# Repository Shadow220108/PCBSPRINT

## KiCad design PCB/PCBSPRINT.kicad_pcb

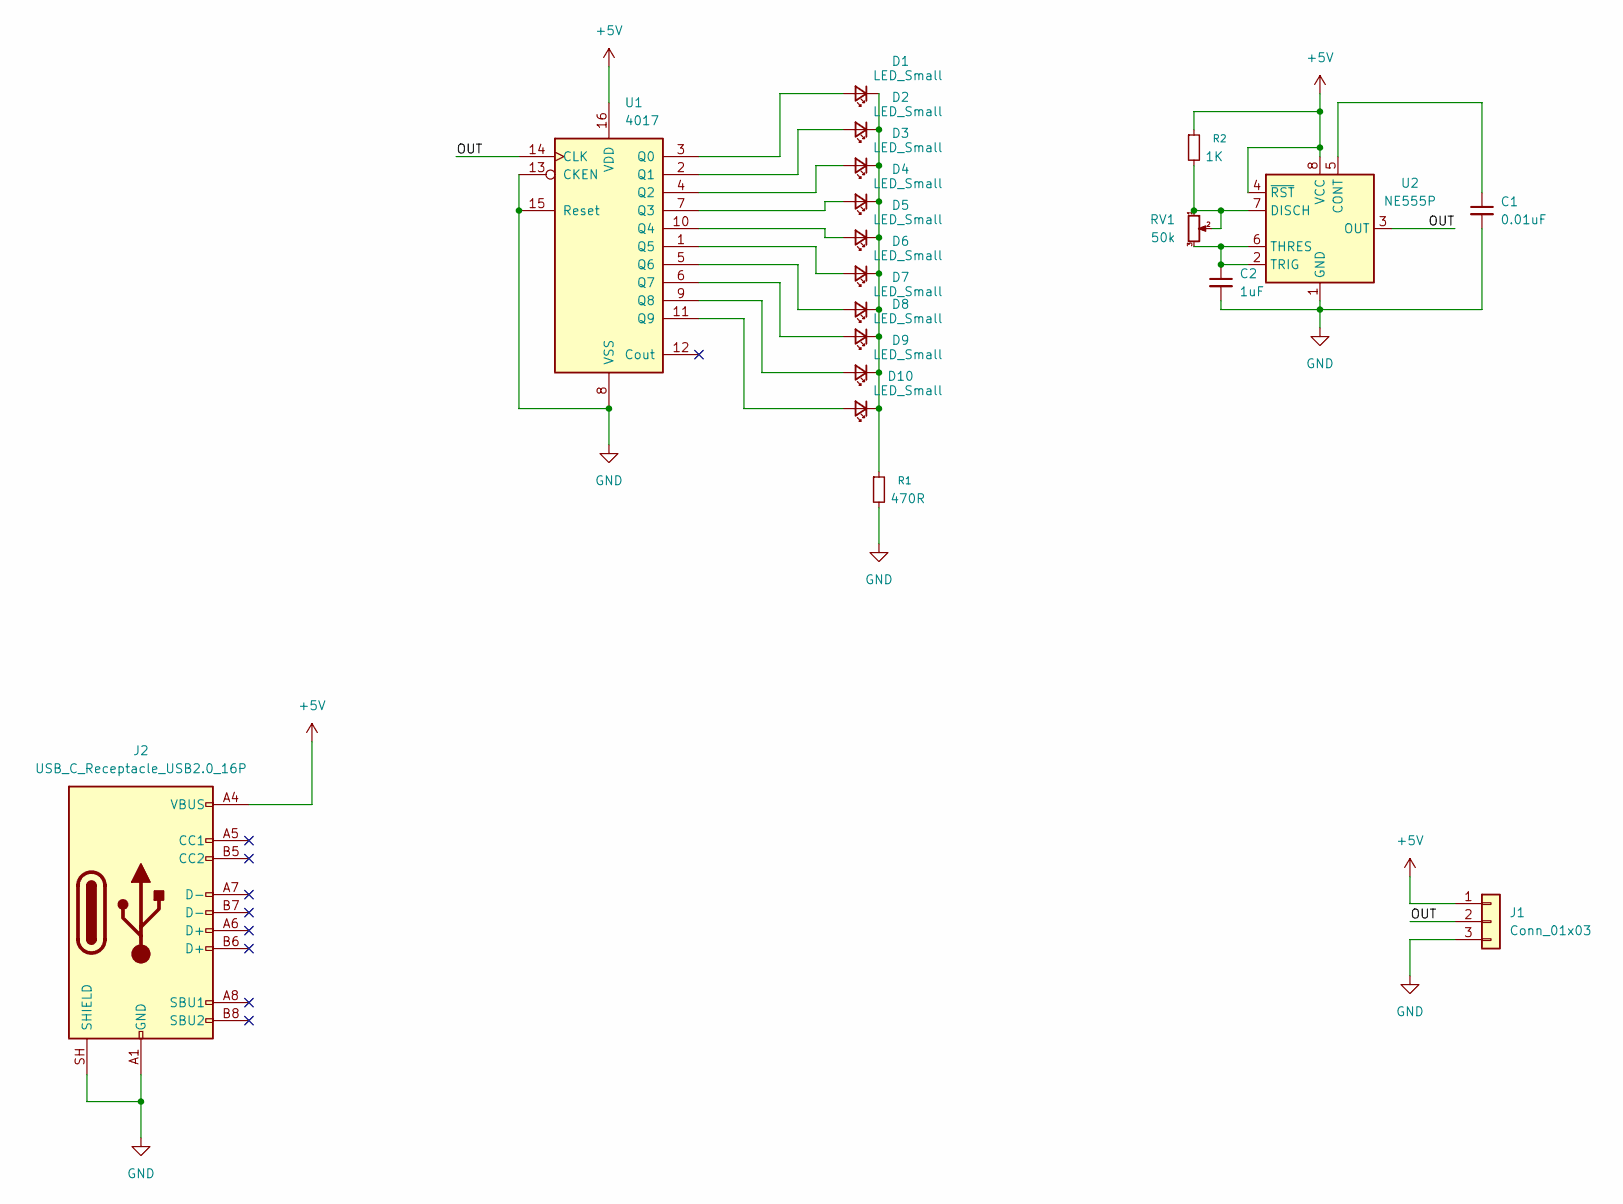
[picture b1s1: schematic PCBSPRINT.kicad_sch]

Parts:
C1: 0.01uF; C_0805_2012Metric_Pad1.18x1.45mm_HandSolder
C2: 1uF; C_0805_2012Metric_Pad1.18x1.45mm_HandSolder
D1, D2, D3, D4, D5, D6, D7, D8, D9, D10: LED_Small; LED_2512_6332Metric_Pad1.52x3.35mm_HandSolder
J1: Conn_01x03; PinHeader_1x03_P2.54mm_Vertical
J2: USB_C_Receptacle_USB2.0_16P; USB_C_Receptacle_HRO_TYPE-C-31-M-12
R1: 470R; R_0805_2012Metric_Pad1.20x1.40mm_HandSolder
R2: 1K; R_0805_2012Metric_Pad1.20x1.40mm_HandSolder
RV1: 50k; Potentiometer_Vishay_T93YA_Vertical
U1: 4017; DIP-16_16P-L20.2-W6.6-P2.54-LS7.6-BL
U2: NE555P; DIP-8_W7.62mm

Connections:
+5V: J1.1, J2.A4 (VBUS), J2.A9 (VBUS), J2.B4 (VBUS), J2.B9 (VBUS), R2.1, U1.16 (VDD), U2.4 (~RST), U2.8 (VCC)
/OUT: J1.2, U1.14 (CLK), U2.3 (OUT)
GND: C1.2, C2.2, J1.3, J2.A1 (GND), J2.A12 (GND), J2.B1 (GND), J2.B12 (GND), J2.SH (SHIELD), R1.2, U1.8 (VSS), U1.13 (CKEN), U1.15 (Reset), U2.1 (GND)
unnamed: D1.2 (A), U1.3 (Q0)
unnamed: D1.1 (K), D2.1 (K), D3.1 (K), D4.1 (K), D5.1 (K), D6.1 (K), D7.1 (K), D8.1 (K), D9.1 (K), D10.1 (K), R1.1
unnamed: D2.2 (A), U1.2 (Q1)
unnamed: D3.2 (A), U1.4 (Q2)
unnamed: D4.2 (A), U1.7 (Q3)
unnamed: D5.2 (A), U1.10 (Q4)
unnamed: D6.2 (A), U1.1 (Q5)
unnamed: D7.2 (A), U1.5 (Q6)
unnamed: D8.2 (A), U1.6 (Q7)
unnamed: D9.2 (A), U1.9 (Q8)
unnamed: D10.2 (A), U1.11 (Q9)
unnamed: C1.1, U2.5 (CONT)
unnamed: R2.2, RV1.1, RV1.2, U2.7 (DISCH)
unnamed: C2.1, RV1.3, U2.2 (TRIG), U2.6 (THRES)

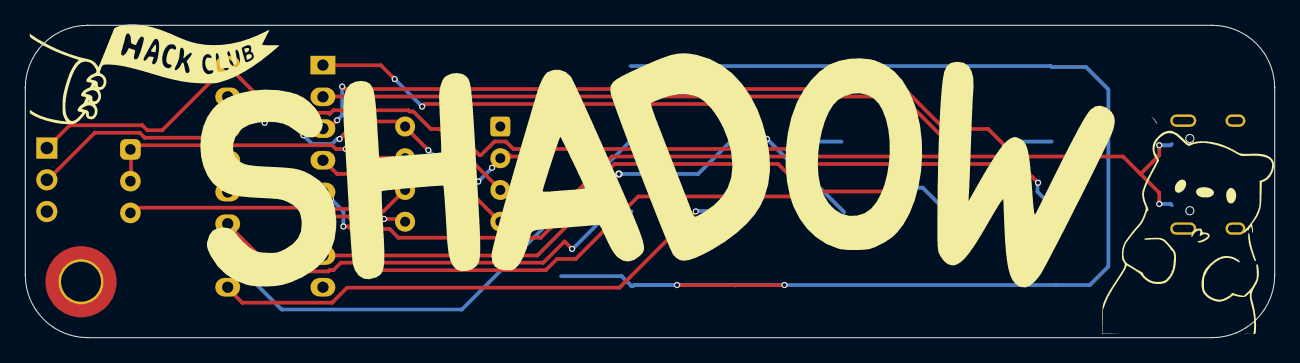
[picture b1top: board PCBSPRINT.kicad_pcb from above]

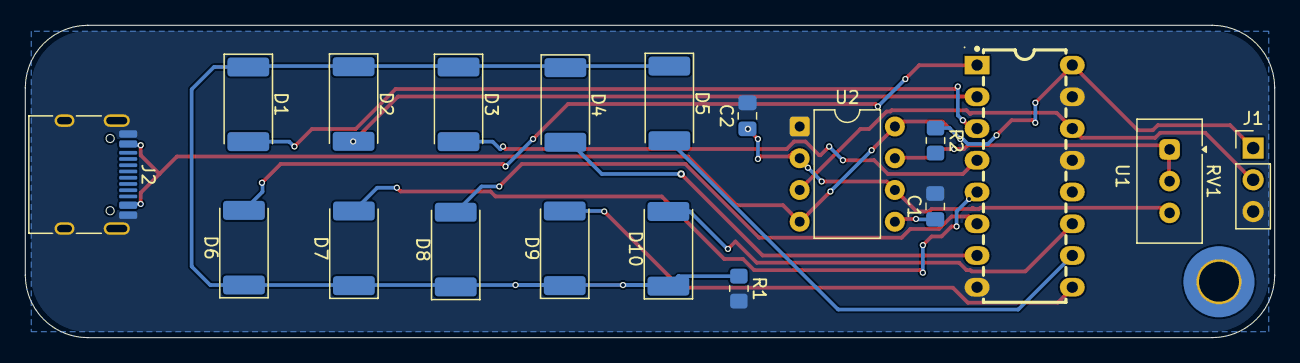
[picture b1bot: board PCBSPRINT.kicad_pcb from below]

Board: 2 copper layers, 100.0 x 25.0 mm, 19 parts (19 on the bottom side), 17 nets.

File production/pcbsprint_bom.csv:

Designator,Footprint,Quantity,Value,LCSC Part #
C1,0805,1,0.01uF,
C2,0805,1,1uF,
"D1, D10, D2, D3, D4, D5, D6, D7, D8, D9",2512,10,LED_Small,
J1,PinHeader_1x03_P2.54mm_Vertical,1,Conn_01x03,
J2,USB_C_Receptacle_HRO_TYPE-C-31-M-12,1,USB_C_Receptacle_USB2.0_16P,
R1,0805,1,470R,
R2,0805,1,1K,
RV1,Potentiometer_Vishay_T93YA_Vertical,1,50k,
U1,DIP-16_16P-L20.2-W6.6-P2.54-LS7.6-BL,1,4017,C34519
U2,DIP-8_W7.62mm,1,NE555P,
